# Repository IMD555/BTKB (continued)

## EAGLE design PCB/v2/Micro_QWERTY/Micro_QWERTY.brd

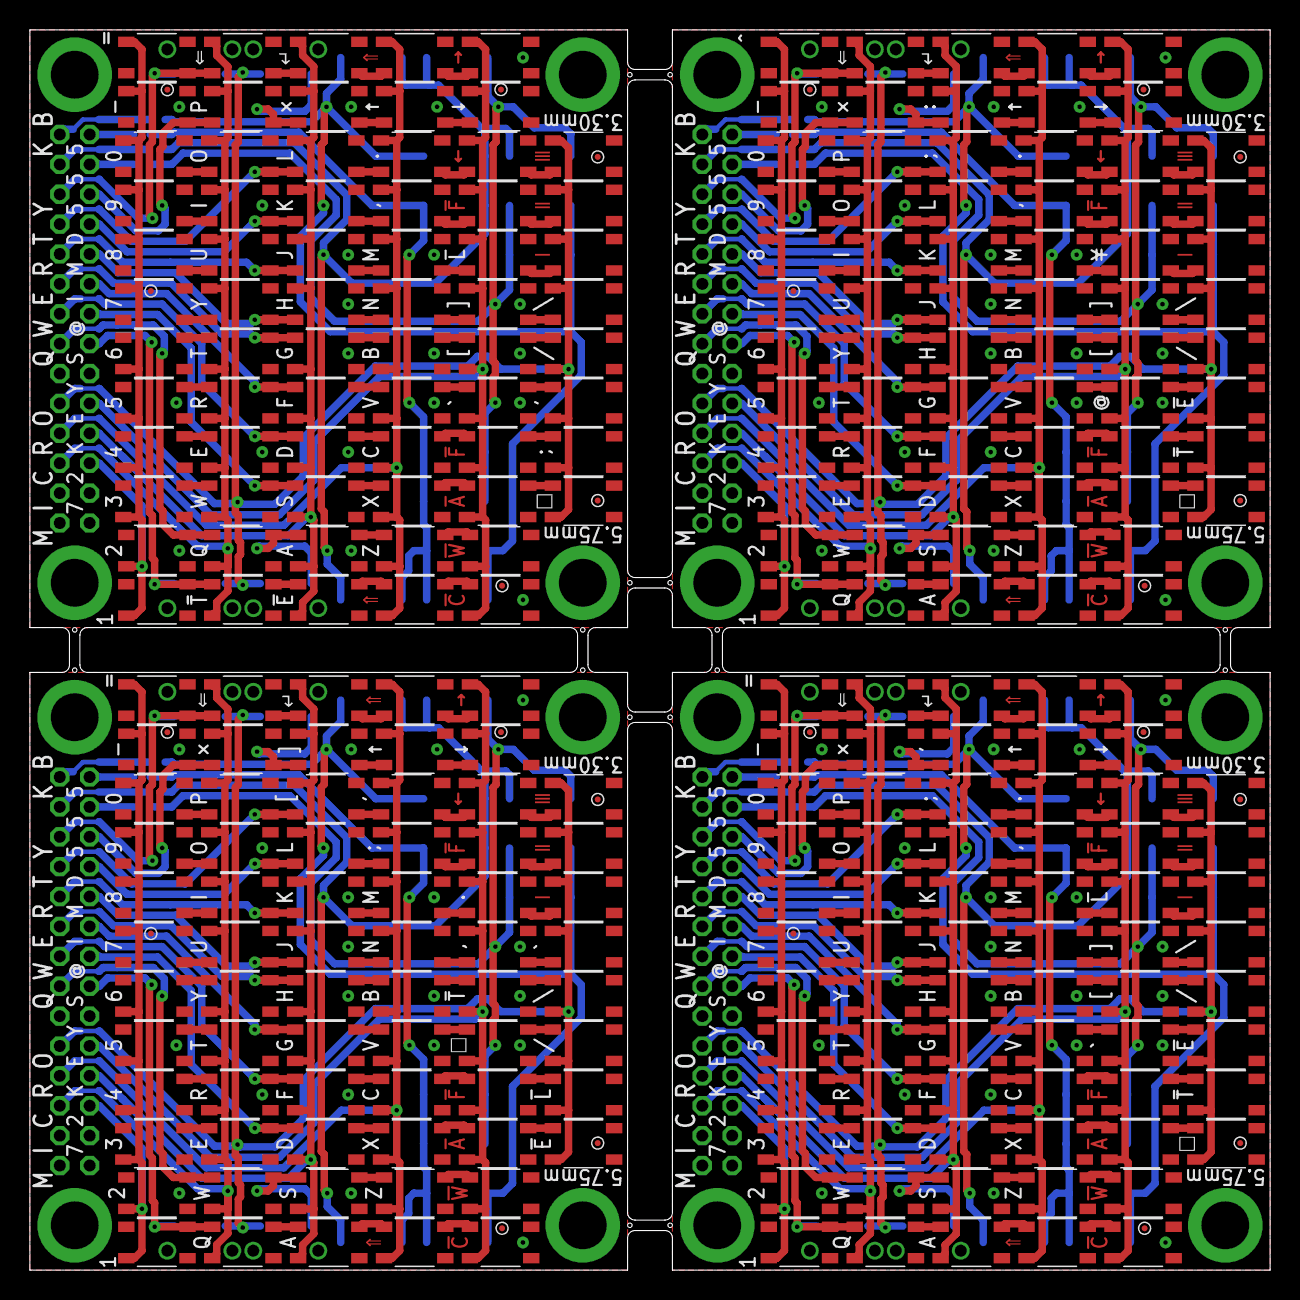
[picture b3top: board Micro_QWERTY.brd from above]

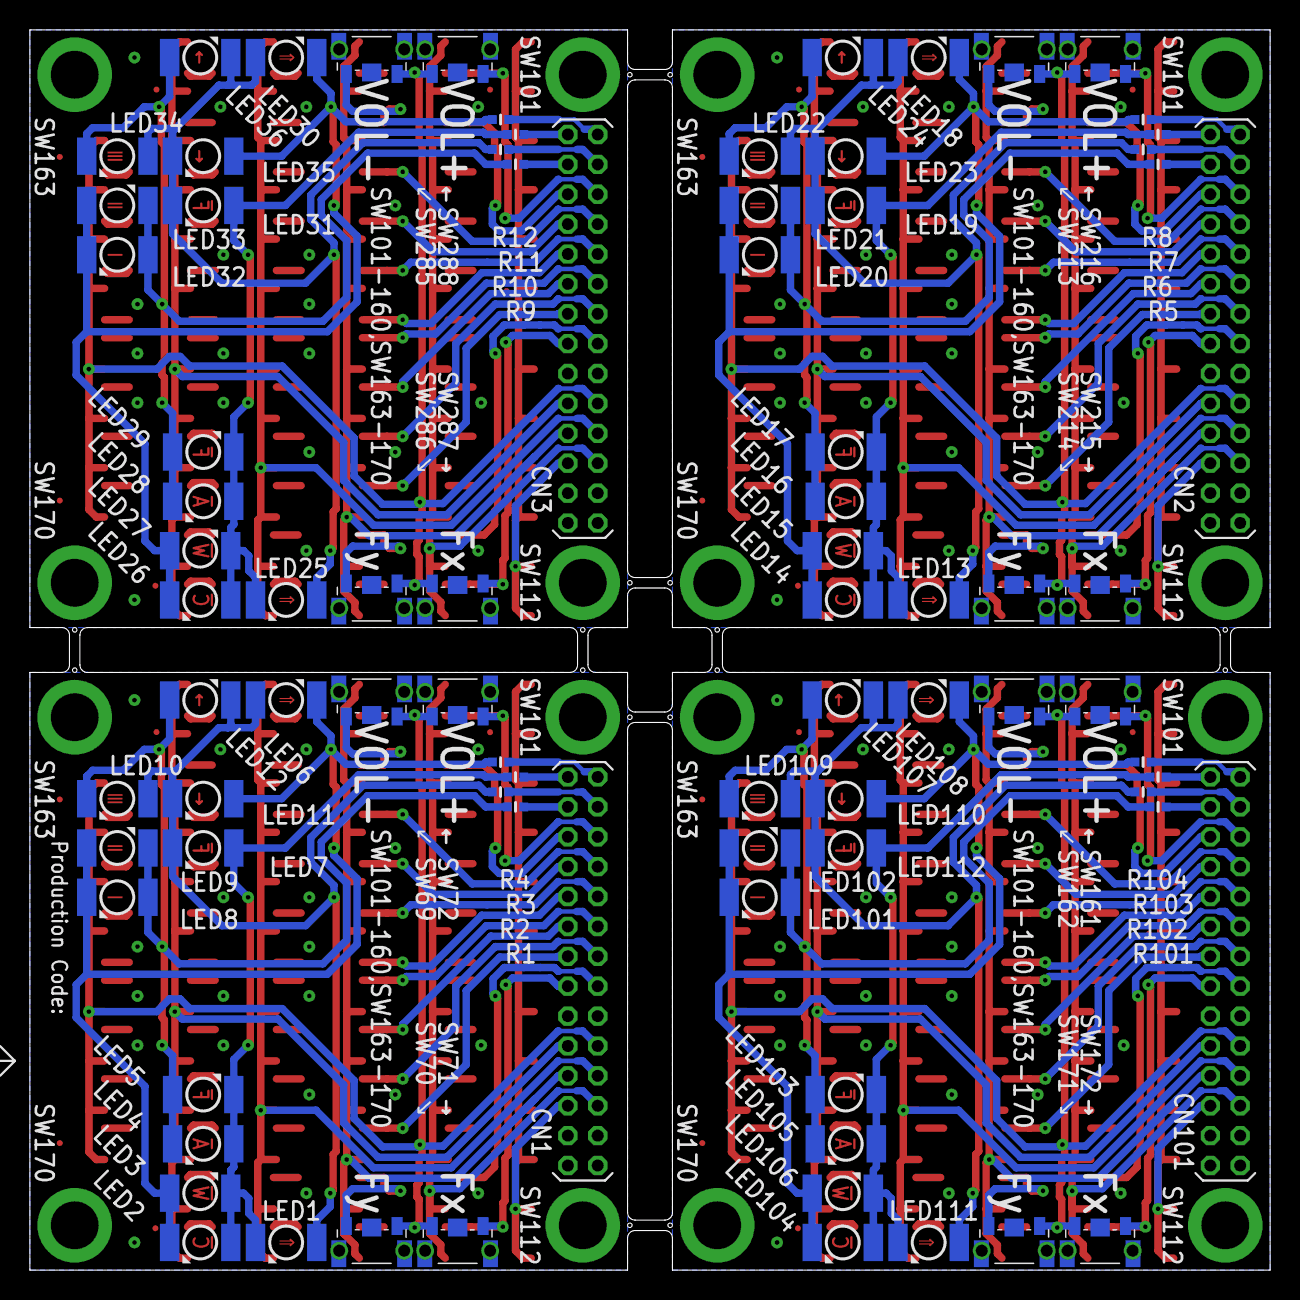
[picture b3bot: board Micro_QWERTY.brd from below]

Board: 2 copper layers, 83.0 x 83.0 mm, 380 parts (84 on the bottom side), 284 nets.

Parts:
CN1, CN2, CN3, CN101: 14X2R; 2MM_14X2_R
LED1, LED13, LED25, LED111: Shift_Left; P-LCC-2-TOPLED-RG-WINDOW
LED2, LED14, LED26, LED104: Ctrl; P-LCC-2-TOPLED-RG-WINDOW
LED3, LED15, LED27, LED106: Win; P-LCC-2-TOPLED-RG-WINDOW
LED4, LED16, LED28, LED105: Alt; P-LCC-2-TOPLED-RG-WINDOW
LED5, LED17, LED29, LED103: Fn_Left; P-LCC-2-TOPLED-RG-WINDOW
LED6, LED18, LED30, LED108: Shift_Right; P-LCC-2-TOPLED-RG-WINDOW
LED7, LED19, LED31, LED112: Fn_Right; P-LCC-2-TOPLED-RG-WINDOW
LED8, LED20, LED32, LED101: M1; P-LCC-2-TOPLED-RG-WINDOW
LED9, LED21, LED33, LED102: M2; P-LCC-2-TOPLED-RG-WINDOW
LED10, LED22, LED34, LED109: M3; P-LCC-2-TOPLED-RG-WINDOW
LED11, LED23, LED35, LED110: Cursor_Left; P-LCC-2-TOPLED-RG-WINDOW
LED12, LED24, LED36, LED107: Cursor_Right; P-LCC-2-TOPLED-RG-WINDOW
R1, R2, R3, R4, R5, R6, R7, R8, R9, R10, R11, R12, R101, R102, R103, R104: R0402-SS
SW1, SW73, SW112, SW217: SKRP(ALPS); TVAU10-025
SW2, SW3, SW4, SW5, SW6, SW7, SW8, SW9, SW10, SW11, SW12, SW13, SW14, SW15, SW16, SW17, SW18, SW19, SW20, SW21, SW22, SW23, SW24, SW25, SW26, SW27, SW28, SW29, SW30, SW31, SW32, SW33, SW34, SW35, SW36, SW37, SW38, SW39, SW40, SW41, SW42, SW43, SW44, SW45, SW46, SW47, SW48, SW49, SW50, SW51, SW52, SW53, SW54, SW55, SW56, SW57, SW58, SW59, SW60, SW61, SW62, SW63, SW64, SW65, SW66, SW67, SW68, SW74, SW75, SW76, SW77, SW78, SW79, SW80, SW81, SW82, SW83, SW84, SW85, SW86, SW87, SW88, SW89, SW90, SW91, SW92, SW93, SW94, SW95, SW96, SW97, SW98, SW99, SW100, SW101, SW102, SW103, SW104, SW105, SW106, SW107, SW108, SW109, SW110, SW111, SW113, SW114, SW115, SW116, SW117, SW118, SW119, SW120, SW121, SW122, SW123, SW124, SW125, SW126, SW127, SW128, SW129, SW130, SW131, SW132, SW133, SW134, SW135, SW136, SW137, SW138, SW139, SW140, SW141, SW142, SW143, SW144, SW145, SW146, SW147, SW148, SW149, SW150, SW151, SW152, SW153, SW154, SW155, SW156, SW157, SW158, SW159, SW160, SW163, SW164, SW165, SW166, SW167, SW168, SW169, SW170, SW173, SW174, SW175, SW176, SW177, SW178, SW179, SW180, SW181, SW182, SW183, SW184, SW185, SW186, SW187, SW188, SW189, SW190, SW191, SW192, SW193, SW194, SW195, SW196, SW197, SW198, SW199, SW200, SW201, SW202, SW203, SW204, SW205, SW206, SW207, SW208, SW209, SW210, SW211, SW212, SW218, SW219, SW220, SW221, SW222, SW223, SW224, SW225, SW226, SW227, SW228, SW229, SW230, SW231, SW232, SW233, SW234, SW235, SW236, SW237, SW238, SW239, SW240, SW241, SW242, SW243, SW244, SW245, SW246, SW247, SW248, SW249, SW250, SW251, SW252, SW253, SW254, SW255, SW256, SW257, SW258, SW259, SW260, SW261, SW262, SW263, SW264, SW265, SW266, SW267, SW268, SW269, SW270, SW271, SW272, SW273, SW274, SW275, SW276, SW277, SW278, SW279, SW280, SW281, SW282, SW283, SW284: SW_4PTVAU10-025; TVAU10-025
SW69, SW70, SW72, SW161, SW162, SW171, SW213, SW214, SW216, SW285, SW286, SW288: SW_WITH_EARTHX; THAM05
SW71, SW172, SW215, SW287: THAM05 or TS-018A; THAM05
U$1, U$2, U$3, U$4, U$5, U$6, U$7, U$8, U$9, U$10, U$11, U$12, U$13, U$14, U$15, U$16, U$17, U$18, U$19, U$20, U$21, U$22, U$23, U$24: PCB_CHECK

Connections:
C0: CN101.13, SW112.P$2, SW124.P$1, SW172.P$1
C1: CN101.14, SW111.P$2, SW123.P$1
C2: CN101.15, SW122.P$2, SW134.P$1
C3: CN101.16, SW121.P$2, SW133.P$1
C4: CN101.17, SW120.P$2, SW132.P$1
C5: CN101.18, SW119.P$2, SW131.P$1
C6: CN101.19, SW118.P$4, SW130.P$3
C7: CN101.20, SW117.P$4, SW129.P$3
C8: CN101.21, SW116.P$4, SW128.P$3
C9: CN101.22, SW115.P$4, SW127.P$3
C10: CN101.23, SW102.P$4, SW114.P$3
C11: CN101.24, SW101.P$4, SW113.P$3, SW161.P$2
C12: CN1.13, SW1.P$2, SW2.P$1, SW71.P$1
C13: CN1.14, SW6.P$2, SW7.P$1
C14: CN1.15, SW12.P$2, SW13.P$1
C15: CN1.16, SW18.P$2, SW19.P$1
C16: CN1.17, SW24.P$2, SW25.P$1
C17: CN1.18, SW30.P$2, SW31.P$1
C18: CN1.19, SW36.P$4, SW37.P$3
C19: CN1.20, SW42.P$4, SW43.P$3
C20: CN1.21, SW48.P$4, SW49.P$3
C21: CN1.22, SW54.P$4, SW55.P$3
C22: CN1.23, SW59.P$4, SW60.P$3
C23: CN1.24, SW64.P$4, SW65.P$3, SW72.P$2
C24: CN2.13, SW73.P$2, SW74.P$1, SW215.P$1
C25: CN2.14, SW78.P$2, SW79.P$1
C26: CN2.15, SW84.P$2, SW85.P$1
C27: CN2.16, SW90.P$2, SW91.P$1
C28: CN2.17, SW96.P$2, SW97.P$1
C29: CN2.18, SW174.P$2, SW175.P$1
C30: CN2.19, SW180.P$4, SW181.P$3
C31: CN2.20, SW186.P$4, SW187.P$3
C32: CN2.21, SW192.P$4, SW193.P$3
C33: CN2.22, SW198.P$4, SW199.P$3
C34: CN2.23, SW203.P$4, SW204.P$3
C35: CN2.24, SW208.P$4, SW209.P$3, SW216.P$2
C36: CN3.13, SW217.P$2, SW218.P$1, SW287.P$1
C37: CN3.14, SW222.P$2, SW223.P$1
C38: CN3.15, SW228.P$2, SW229.P$1
C39: CN3.16, SW234.P$2, SW235.P$1
C40: CN3.17, SW240.P$2, SW241.P$1
C41: CN3.18, SW246.P$2, SW247.P$1
C42: CN3.19, SW252.P$4, SW253.P$3
C43: CN3.20, SW258.P$4, SW259.P$3
C44: CN3.21, SW264.P$4, SW265.P$3
C45: CN3.22, SW270.P$4, SW271.P$3
C46: CN3.23, SW275.P$4, SW276.P$3
C47: CN3.24, SW280.P$4, SW281.P$3, SW288.P$2
GND: CN101.2, CN101.4, SW161.S1, SW161.S2, SW161.S3, SW161.S4, SW161.S5, SW162.S1, SW162.S2, SW162.S3, SW162.S4, SW162.S5, SW171.S1, SW171.S2, SW171.S3, SW171.S4, SW171.S5, SW172.S1, SW172.S2, SW172.S3, SW172.S4, SW172.S5
GND1: CN1.2, CN1.4, SW69.S1, SW69.S2, SW69.S3, SW69.S4, SW69.S5, SW70.S1, SW70.S2, SW70.S3, SW70.S4, SW70.S5, SW71.S1, SW71.S2, SW71.S3, SW71.S4, SW71.S5, SW72.S1, SW72.S2, SW72.S3, SW72.S4, SW72.S5
GND2: CN2.2, CN2.4, SW213.S1, SW213.S2, SW213.S3, SW213.S4, SW213.S5, SW214.S1, SW214.S2, SW214.S3, SW214.S4, SW214.S5, SW215.S1, SW215.S2, SW215.S3, SW215.S4, SW215.S5, SW216.S1, SW216.S2, SW216.S3, SW216.S4, SW216.S5
GND3: CN3.2, CN3.4, SW285.S1, SW285.S2, SW285.S3, SW285.S4, SW285.S5, SW286.S1, SW286.S2, SW286.S3, SW286.S4, SW286.S5, SW287.S1, SW287.S2, SW287.S3, SW287.S4, SW287.S5, SW288.S1, SW288.S2, SW288.S3, SW288.S4, SW288.S5
L0: CN101.28, R104.2
L1: CN101.27, R103.2
L2: CN101.26, R102.2
L3: CN101.25, R101.2
L4: CN1.26, R2.2
L5: CN1.28, R4.2
L6: CN1.25, R1.2
L7: CN1.27, R3.2
L8: CN2.26, R6.2
L9: CN2.28, R8.2
L10: CN2.25, R5.2
L11: CN2.27, R7.2
L12: CN3.26, R10.2
L13: CN3.28, R12.2
L14: CN3.25, R9.2
L15: CN3.27, R11.2
unnamed: LED107.C, LED108.A, LED109.A, LED110.C, LED111.A, LED112.C, R102.1
unnamed: LED101.A, LED102.C, LED103.A, LED105.C, LED107.A, LED109.C, R101.1
unnamed: LED103.C, LED104.A, LED105.A, LED106.C, LED111.C, LED112.A, R103.1
unnamed: LED101.C, LED102.A, LED104.C, LED106.A, LED108.C, LED110.A, R104.1
unnamed: SW123.P$2, SW135.P$1, SW171.P$2
unnamed: SW113.P$4, SW125.P$3
unnamed: SW114.P$4, SW126.P$3, SW162.P$1
unnamed: SW29.P$2, SW30.P$1
unnamed: SW106.P$4, SW118.P$3
unnamed: SW130.P$4, SW142.P$3
unnamed: SW154.P$4, SW166.P$3
unnamed: SW142.P$4, SW154.P$3
unnamed: SW105.P$4, SW117.P$3
unnamed: SW129.P$4, SW141.P$3
unnamed: SW153.P$4, SW165.P$3
unnamed: SW141.P$4, SW153.P$3
unnamed: SW104.P$4, SW116.P$3
unnamed: SW128.P$4, SW140.P$3
unnamed: SW152.P$4, SW164.P$3
unnamed: SW140.P$4, SW152.P$3
unnamed: SW103.P$4, SW115.P$3
unnamed: SW127.P$4, SW139.P$3
unnamed: SW151.P$4, SW163.P$3
unnamed: SW139.P$4, SW151.P$3
unnamed: SW31.P$2, SW32.P$1
unnamed: SW126.P$4, SW138.P$3
unnamed: SW32.P$2, SW33.P$1
unnamed: SW138.P$4, SW150.P$3
unnamed: SW33.P$2, SW34.P$1
unnamed: SW125.P$4, SW137.P$3
unnamed: SW2.P$2, SW3.P$1
unnamed: SW137.P$4, SW149.P$3
unnamed: SW3.P$2, SW4.P$1
unnamed: SW4.P$2, SW5.P$1
unnamed: SW8.P$2, SW9.P$1
unnamed: SW9.P$2, SW10.P$1
unnamed: SW11.P$2, SW12.P$1
unnamed: SW13.P$2, SW14.P$1
unnamed: SW14.P$2, SW15.P$1
unnamed: SW15.P$2, SW16.P$1
unnamed: SW107.P$2, SW119.P$1
unnamed: SW17.P$2, SW18.P$1
unnamed: SW131.P$2, SW143.P$1
unnamed: SW155.P$2, SW167.P$1
unnamed: SW143.P$2, SW155.P$1
unnamed: SW108.P$2, SW120.P$1
unnamed: SW19.P$2, SW20.P$1
unnamed: SW132.P$2, SW144.P$1
unnamed: SW156.P$2, SW168.P$1
unnamed: SW144.P$2, SW156.P$1
unnamed: SW109.P$2, SW121.P$1
unnamed: SW20.P$2, SW21.P$1
unnamed: SW133.P$2, SW145.P$1
unnamed: SW157.P$2, SW169.P$1
unnamed: SW145.P$2, SW157.P$1
unnamed: SW110.P$2, SW122.P$1
unnamed: SW21.P$2, SW22.P$1
unnamed: SW134.P$2, SW146.P$1
unnamed: SW158.P$2, SW170.P$1
unnamed: SW146.P$2, SW158.P$1
unnamed: SW23.P$2, SW24.P$1
unnamed: SW25.P$2, SW26.P$1
unnamed: SW26.P$2, SW27.P$1
unnamed: SW27.P$2, SW28.P$1
unnamed: LED1.A, LED6.A, LED7.C, LED10.A, LED11.C, LED12.C, R2.1
unnamed: LED4.C, LED5.A, LED8.A, LED9.C, LED10.C, LED12.A, R1.1
unnamed: LED1.C, LED2.A, LED3.C, LED4.A, LED5.C, LED7.A, R3.1
unnamed: SW135.P$2, SW147.P$1
unnamed: LED2.C, LED3.A, LED6.C, LED8.C, LED9.A, LED11.A, R4.1
unnamed: SW147.P$2, SW159.P$1
unnamed: SW41.P$4, SW42.P$3
unnamed: SW124.P$2, SW136.P$1
unnamed: SW136.P$2, SW148.P$1
unnamed: SW43.P$4, SW44.P$3
unnamed: SW148.P$2, SW160.P$1
unnamed: SW44.P$4, SW45.P$3
unnamed: SW45.P$4, SW46.P$3
unnamed: SW47.P$4, SW48.P$3
unnamed: SW49.P$4, SW50.P$3
unnamed: SW50.P$4, SW51.P$3
unnamed: SW51.P$4, SW52.P$3
unnamed: SW53.P$4, SW54.P$3
unnamed: SW55.P$4, SW56.P$3
unnamed: SW56.P$4, SW57.P$3
unnamed: SW57.P$4, SW58.P$3
unnamed: SW61.P$4, SW62.P$3
unnamed: SW62.P$4, SW63.P$3
unnamed: SW66.P$4, SW67.P$3
unnamed: SW67.P$4, SW68.P$3
unnamed: SW35.P$4, SW36.P$3
unnamed: SW37.P$4, SW38.P$3
unnamed: SW38.P$4, SW39.P$3
unnamed: SW39.P$4, SW40.P$3
unnamed: SW7.P$2, SW8.P$1, SW70.P$2
unnamed: SW65.P$4, SW66.P$3
unnamed: SW60.P$4, SW61.P$3, SW69.P$1
unnamed: SW173.P$2, SW174.P$1
unnamed: SW175.P$2, SW176.P$1
unnamed: SW176.P$2, SW177.P$1
unnamed: SW177.P$2, SW178.P$1
unnamed: SW74.P$2, SW75.P$1
unnamed: SW75.P$2, SW76.P$1
unnamed: SW76.P$2, SW77.P$1
unnamed: SW80.P$2, SW81.P$1
unnamed: SW81.P$2, SW82.P$1
unnamed: SW83.P$2, SW84.P$1
unnamed: SW85.P$2, SW86.P$1
unnamed: SW86.P$2, SW87.P$1
unnamed: SW87.P$2, SW88.P$1
unnamed: SW89.P$2, SW90.P$1
unnamed: SW91.P$2, SW92.P$1
unnamed: SW92.P$2, SW93.P$1
unnamed: SW93.P$2, SW94.P$1
unnamed: SW95.P$2, SW96.P$1
unnamed: SW97.P$2, SW98.P$1
unnamed: SW98.P$2, SW99.P$1
unnamed: SW99.P$2, SW100.P$1
unnamed: LED13.A, LED18.A, LED19.C, LED22.A, LED23.C, LED24.C, R6.1
unnamed: LED16.C, LED17.A, LED20.A, LED21.C, LED22.C, LED24.A, R5.1
unnamed: LED13.C, LED14.A, LED15.C, LED16.A, LED17.C, LED19.A, R7.1
unnamed: LED14.C, LED15.A, LED18.C, LED20.C, LED21.A, LED23.A, R8.1
unnamed: SW185.P$4, SW186.P$3
unnamed: SW187.P$4, SW188.P$3
unnamed: SW188.P$4, SW189.P$3
unnamed: SW189.P$4, SW190.P$3
unnamed: SW191.P$4, SW192.P$3
unnamed: SW193.P$4, SW194.P$3
unnamed: SW194.P$4, SW195.P$3
unnamed: SW195.P$4, SW196.P$3
unnamed: SW197.P$4, SW198.P$3
unnamed: SW199.P$4, SW200.P$3
unnamed: SW200.P$4, SW201.P$3
unnamed: SW201.P$4, SW202.P$3
unnamed: SW205.P$4, SW206.P$3
unnamed: SW206.P$4, SW207.P$3
unnamed: SW210.P$4, SW211.P$3
unnamed: SW211.P$4, SW212.P$3
unnamed: SW179.P$4, SW180.P$3
unnamed: SW181.P$4, SW182.P$3
unnamed: SW182.P$4, SW183.P$3
unnamed: SW183.P$4, SW184.P$3
unnamed: SW79.P$2, SW80.P$1, SW214.P$2
unnamed: SW209.P$4, SW210.P$3
unnamed: SW204.P$4, SW205.P$3, SW213.P$1
unnamed: SW245.P$2, SW246.P$1
unnamed: SW247.P$2, SW248.P$1
unnamed: SW248.P$2, SW249.P$1
unnamed: SW249.P$2, SW250.P$1
unnamed: SW218.P$2, SW219.P$1
unnamed: SW219.P$2, SW220.P$1
unnamed: SW220.P$2, SW221.P$1
unnamed: SW224.P$2, SW225.P$1
unnamed: SW225.P$2, SW226.P$1
unnamed: SW227.P$2, SW228.P$1
unnamed: SW229.P$2, SW230.P$1
unnamed: SW230.P$2, SW231.P$1
unnamed: SW231.P$2, SW232.P$1
unnamed: SW233.P$2, SW234.P$1
unnamed: SW235.P$2, SW236.P$1
unnamed: SW236.P$2, SW237.P$1
unnamed: SW237.P$2, SW238.P$1
unnamed: SW239.P$2, SW240.P$1
unnamed: SW241.P$2, SW242.P$1
unnamed: SW242.P$2, SW243.P$1
unnamed: SW243.P$2, SW244.P$1
unnamed: LED25.A, LED30.A, LED31.C, LED34.A, LED35.C, LED36.C, R10.1
unnamed: LED28.C, LED29.A, LED32.A, LED33.C, LED34.C, LED36.A, R9.1
unnamed: LED25.C, LED26.A, LED27.C, LED28.A, LED29.C, LED31.A, R11.1
unnamed: LED26.C, LED27.A, LED30.C, LED32.C, LED33.A, LED35.A, R12.1
unnamed: SW257.P$4, SW258.P$3
unnamed: SW259.P$4, SW260.P$3
unnamed: SW260.P$4, SW261.P$3
unnamed: SW261.P$4, SW262.P$3
unnamed: SW263.P$4, SW264.P$3
unnamed: SW265.P$4, SW266.P$3
unnamed: SW266.P$4, SW267.P$3
unnamed: SW267.P$4, SW268.P$3
unnamed: SW269.P$4, SW270.P$3
unnamed: SW271.P$4, SW272.P$3
unnamed: SW272.P$4, SW273.P$3
unnamed: SW273.P$4, SW274.P$3
unnamed: SW277.P$4, SW278.P$3
unnamed: SW278.P$4, SW279.P$3
unnamed: SW282.P$4, SW283.P$3
unnamed: SW283.P$4, SW284.P$3
unnamed: SW251.P$4, SW252.P$3
unnamed: SW253.P$4, SW254.P$3
unnamed: SW254.P$4, SW255.P$3
unnamed: SW255.P$4, SW256.P$3
unnamed: SW223.P$2, SW224.P$1, SW286.P$2
unnamed: SW281.P$4, SW282.P$3
unnamed: SW276.P$4, SW277.P$3, SW285.P$1
R0: CN101.5, SW101.P$1, SW102.P$1, SW103.P$1, SW104.P$1, SW105.P$1, SW106.P$1, SW107.P$3, SW108.P$3, SW109.P$3, SW110.P$3, SW111.P$3, SW112.P$3
R1: CN101.6, SW113.P$1, SW114.P$1, SW115.P$1, SW116.P$1, SW117.P$1, SW118.P$1, SW119.P$3, SW120.P$3, SW121.P$3, SW122.P$3, SW123.P$3, SW124.P$3
R2: CN101.7, SW125.P$1, SW126.P$1, SW127.P$1, SW128.P$1, SW129.P$1, SW130.P$1, SW131.P$3, SW132.P$3, SW133.P$3, SW134.P$3, SW135.P$3, SW136.P$3
R3: CN101.8, SW137.P$1, SW138.P$1, SW139.P$1, SW140.P$1, SW141.P$1, SW142.P$1, SW143.P$3, SW144.P$3, SW145.P$3, SW146.P$3, SW147.P$3, SW148.P$3
R4: CN101.9, SW149.P$1, SW150.P$1, SW151.P$1, SW152.P$1, SW153.P$1, SW154.P$1, SW155.P$3, SW156.P$3, SW157.P$3, SW158.P$3, SW159.P$3, SW160.P$3
R5: CN101.10, SW161.P$1, SW162.P$2, SW163.P$1, SW164.P$1, SW165.P$1, SW166.P$1, SW167.P$3, SW168.P$3, SW169.P$3, SW170.P$3, SW171.P$1, SW172.P$2
R6: CN1.5, SW1.P$3, SW6.P$3, SW11.P$3, SW17.P$3, SW23.P$3, SW29.P$3, SW35.P$1, SW41.P$1, SW47.P$1, SW53.P$1, SW59.P$1, SW64.P$1
R7: CN1.6, SW2.P$3, SW7.P$3, SW12.P$3, SW18.P$3, SW24.P$3, SW30.P$3, SW36.P$1, SW42.P$1, SW48.P$1, SW54.P$1, SW60.P$1, SW65.P$1
R8: CN1.7, SW3.P$3, SW8.P$3, SW13.P$3, SW19.P$3, SW25.P$3, SW31.P$3, SW37.P$1, SW43.P$1, SW49.P$1, SW55.P$1, SW61.P$1, SW66.P$1
R9: CN1.8, SW4.P$3, SW9.P$3, SW14.P$3, SW20.P$3, SW26.P$3, SW32.P$3, SW38.P$1, SW44.P$1, SW50.P$1, SW56.P$1, SW62.P$1, SW67.P$1
R10: CN1.9, SW5.P$3, SW10.P$3, SW15.P$3, SW21.P$3, SW27.P$3, SW33.P$3, SW39.P$1, SW45.P$1, SW51.P$1, SW57.P$1, SW63.P$1, SW68.P$1
R11: CN1.10, SW16.P$3, SW22.P$3, SW28.P$3, SW34.P$3, SW40.P$1, SW46.P$1, SW52.P$1, SW58.P$1, SW69.P$2, SW70.P$1, SW71.P$2, SW72.P$1
R12: CN2.5, SW73.P$3, SW78.P$3, SW83.P$3, SW89.P$3, SW95.P$3, SW173.P$3, SW179.P$1, SW185.P$1, SW191.P$1, SW197.P$1, SW203.P$1, SW208.P$1
R13: CN2.6, SW74.P$3, SW79.P$3, SW84.P$3, SW90.P$3, SW96.P$3, SW174.P$3, SW180.P$1, SW186.P$1, SW192.P$1, SW198.P$1, SW204.P$1, SW209.P$1
R14: CN2.7, SW75.P$3, SW80.P$3, SW85.P$3, SW91.P$3, SW97.P$3, SW175.P$3, SW181.P$1, SW187.P$1, SW193.P$1, SW199.P$1, SW205.P$1, SW210.P$1
R15: CN2.8, SW76.P$3, SW81.P$3, SW86.P$3, SW92.P$3, SW98.P$3, SW176.P$3, SW182.P$1, SW188.P$1, SW194.P$1, SW200.P$1, SW206.P$1, SW211.P$1
R16: CN2.9, SW77.P$3, SW82.P$3, SW87.P$3, SW93.P$3, SW99.P$3, SW177.P$3, SW183.P$1, SW189.P$1, SW195.P$1, SW201.P$1, SW207.P$1, SW212.P$1
R17: CN2.10, SW88.P$3, SW94.P$3, SW100.P$3, SW178.P$3, SW184.P$1, SW190.P$1, SW196.P$1, SW202.P$1, SW213.P$2, SW214.P$1, SW215.P$2, SW216.P$1
R18: CN3.5, SW217.P$3, SW222.P$3, SW227.P$3, SW233.P$3, SW239.P$3, SW245.P$3, SW251.P$1, SW257.P$1, SW263.P$1, SW269.P$1, SW275.P$1, SW280.P$1
R19: CN3.6, SW218.P$3, SW223.P$3, SW228.P$3, SW234.P$3, SW240.P$3, SW246.P$3, SW252.P$1, SW258.P$1, SW264.P$1, SW270.P$1, SW276.P$1, SW281.P$1
R20: CN3.7, SW219.P$3, SW224.P$3, SW229.P$3, SW235.P$3, SW241.P$3, SW247.P$3, SW253.P$1, SW259.P$1, SW265.P$1, SW271.P$1, SW277.P$1, SW282.P$1
R21: CN3.8, SW220.P$3, SW225.P$3, SW230.P$3, SW236.P$3, SW242.P$3, SW248.P$3, SW254.P$1, SW260.P$1, SW266.P$1, SW272.P$1, SW278.P$1, SW283.P$1
R22: CN3.9, SW221.P$3, SW226.P$3, SW231.P$3, SW237.P$3, SW243.P$3, SW249.P$3, SW255.P$1, SW261.P$1, SW267.P$1, SW273.P$1, SW279.P$1, SW284.P$1
R23: CN3.10, SW232.P$3, SW238.P$3, SW244.P$3, SW250.P$3, SW256.P$1, SW262.P$1, SW268.P$1, SW274.P$1, SW285.P$2, SW286.P$1, SW287.P$2, SW288.P$1

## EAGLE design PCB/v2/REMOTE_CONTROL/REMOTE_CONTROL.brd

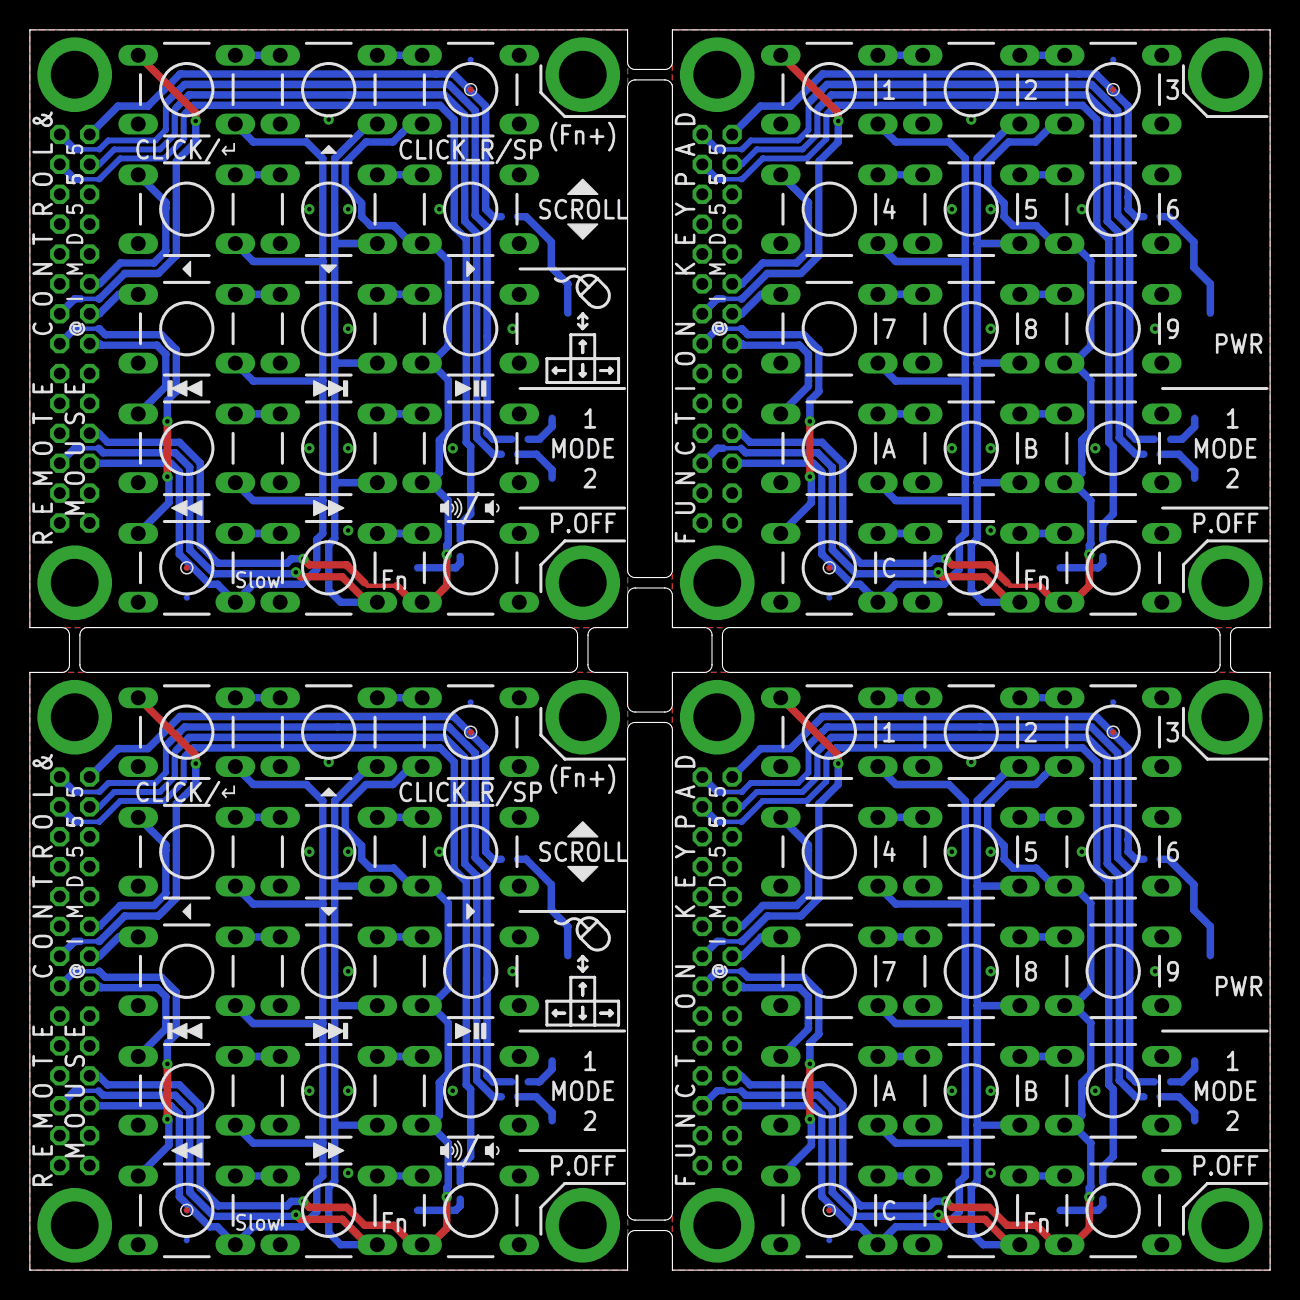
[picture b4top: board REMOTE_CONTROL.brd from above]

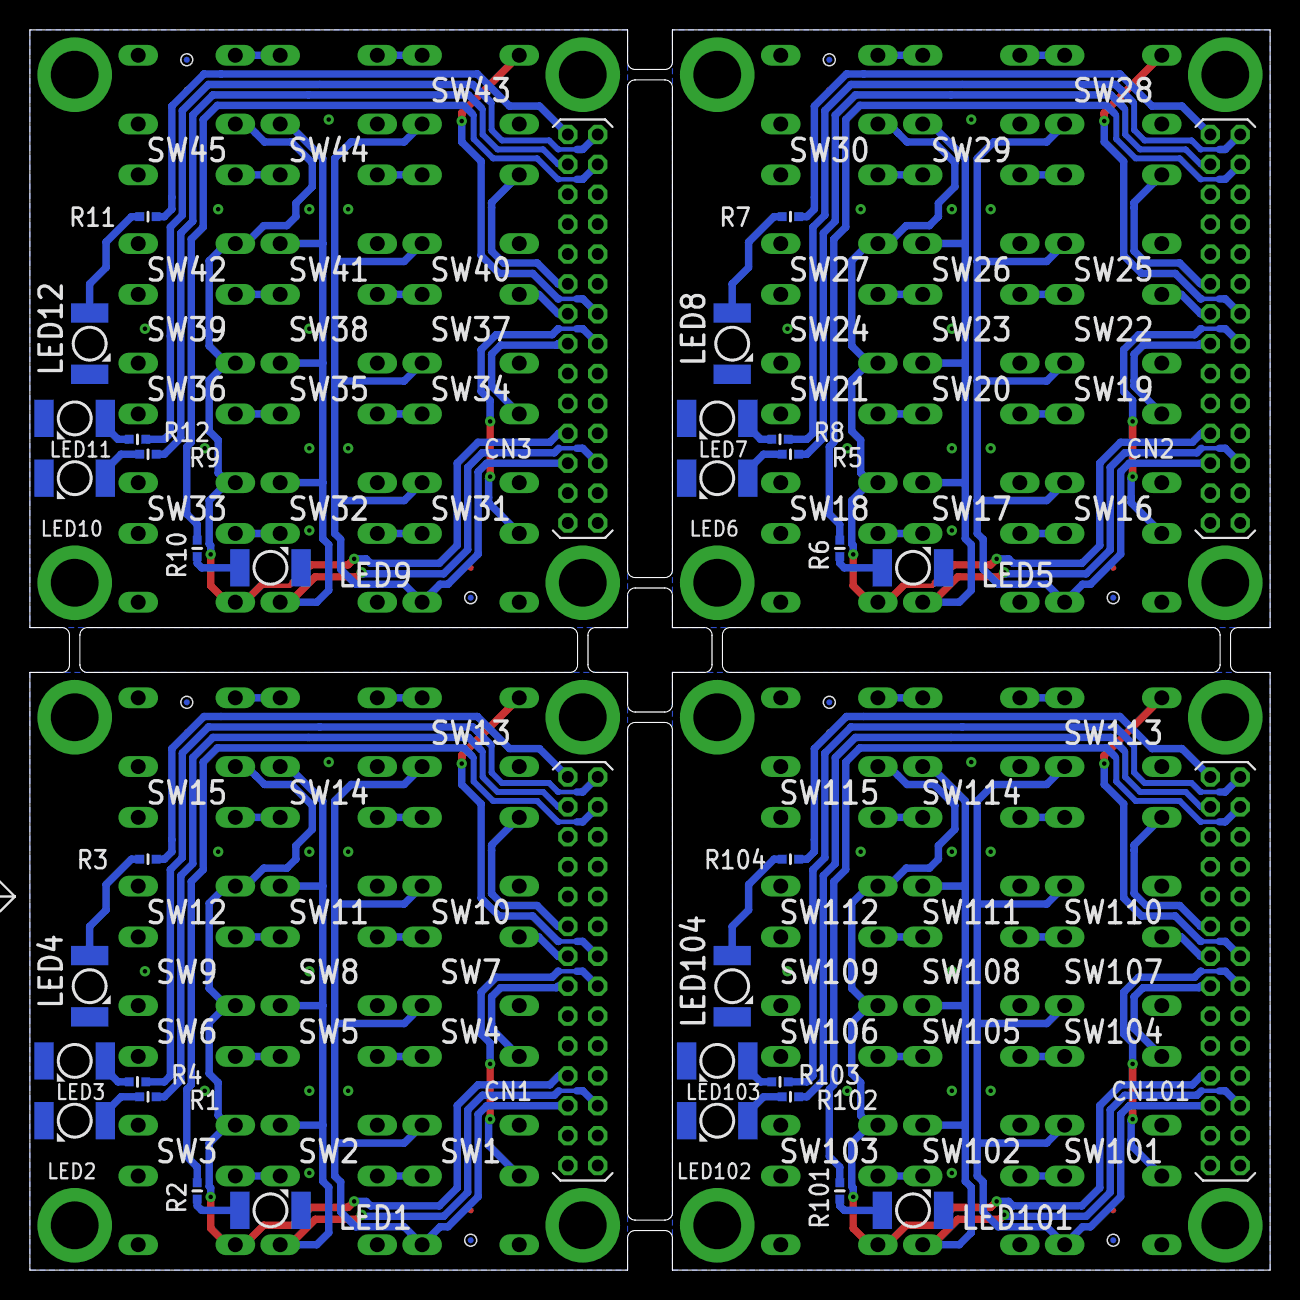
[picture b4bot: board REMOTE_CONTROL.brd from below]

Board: 2 copper layers, 83.0 x 83.0 mm, 112 parts (44 on the bottom side), 108 nets.

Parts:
CN1, CN2, CN3, CN101: 14X2R; 2MM_14X2_R
LED1, LED2, LED3, LED4, LED5, LED6, LED7, LED8, LED9, LED10, LED11, LED12, LED101, LED102, LED103, LED104: P-LCC-2-TOPLED-RG
R1, R2, R3, R4, R5, R6, R7, R8, R9, R10, R11, R12, R101, R102, R103, R104: R0402-SS
SW1, SW2, SW3, SW4, SW5, SW6, SW7, SW8, SW9, SW10, SW11, SW12, SW13, SW14, SW15, SW16, SW17, SW18, SW19, SW20, SW21, SW22, SW23, SW24, SW25, SW26, SW27, SW28, SW29, SW30, SW31, SW32, SW33, SW34, SW35, SW36, SW37, SW38, SW39, SW40, SW41, SW42, SW43, SW44, SW45, SW101, SW102, SW103, SW104, SW105, SW106, SW107, SW108, SW109, SW110, SW111, SW112, SW113, SW114, SW115: DTS-6
U$1, U$2, U$3, U$4, U$5, U$6, U$7, U$8, U$9, U$10, U$11, U$12, U$13, U$14, U$15, U$16: PCB_CHECK

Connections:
C0: CN101.13, SW104.1
C1: CN101.14, SW101.1
C2: CN101.15, SW107.1
C3: CN101.16, SW113.1
C4: CN101.17, SW110.1
C12: CN1.13, SW4.1
C13: CN1.14, SW1.1
C14: CN1.15, SW7.1
C15: CN1.16, SW13.1
C16: CN1.17, SW10.1
C24: CN2.13, SW19.1
C25: CN2.14, SW16.1
C26: CN2.15, SW22.1
C27: CN2.16, SW28.1
C28: CN2.17, SW25.1
C36: CN3.13, SW34.1
C37: CN3.14, SW31.1
C38: CN3.15, SW37.1
C39: CN3.16, SW43.1
C40: CN3.17, SW40.1
GND: CN101.2, CN101.4, LED101.C, LED102.C, LED103.C, LED104.C
GND1: CN1.2, CN1.4, LED1.C, LED2.C, LED3.C, LED4.C
GND2: CN2.2, CN2.4, LED5.C, LED6.C, LED7.C, LED8.C
GND3: CN3.2, CN3.4, LED9.C, LED10.C, LED11.C, LED12.C
L0: CN101.25, R102.2
L1: CN101.26, R101.2
L2: CN101.27, R104.2
L3: CN101.28, R103.2
L4: CN1.26, R2.2
L5: CN1.28, R4.2
L6: CN1.25, R1.2
L7: CN1.27, R3.2
L8: CN2.26, R6.2
L9: CN2.28, R8.2
L10: CN2.25, R5.2
L11: CN2.27, R7.2
L12: CN3.26, R10.2
L13: CN3.28, R12.2
L14: CN3.25, R9.2
L15: CN3.27, R11.2
unnamed: LED104.A, R104.1
unnamed: SW114.2, SW115.1
unnamed: LED103.A, R103.1
unnamed: SW111.2, SW112.1
unnamed: SW108.2, SW109.1
unnamed: LED102.A, R102.1
unnamed: LED101.A, R101.1
unnamed: SW102.2, SW103.1
unnamed: SW105.2, SW106.1
unnamed: SW14.2, SW15.1
unnamed: SW110.2, SW111.1
unnamed: SW107.2, SW108.1
unnamed: SW104.2, SW105.1
unnamed: SW101.2, SW102.1
unnamed: SW113.2, SW114.1
unnamed: SW11.2, SW12.1
unnamed: SW8.2, SW9.1
unnamed: SW2.2, SW3.1
unnamed: SW5.2, SW6.1
unnamed: SW10.2, SW11.1
unnamed: SW7.2, SW8.1
unnamed: SW4.2, SW5.1
unnamed: SW1.2, SW2.1
unnamed: SW13.2, SW14.1
unnamed: LED4.A, R3.1
unnamed: LED3.A, R4.1
unnamed: LED2.A, R1.1
unnamed: LED1.A, R2.1
unnamed: SW29.2, SW30.1
unnamed: SW26.2, SW27.1
unnamed: SW23.2, SW24.1
unnamed: SW17.2, SW18.1
unnamed: SW20.2, SW21.1
unnamed: SW25.2, SW26.1
unnamed: SW22.2, SW23.1
unnamed: SW19.2, SW20.1
unnamed: SW16.2, SW17.1
unnamed: SW28.2, SW29.1
unnamed: LED8.A, R7.1
unnamed: LED7.A, R8.1
unnamed: LED6.A, R5.1
unnamed: LED5.A, R6.1
unnamed: SW44.2, SW45.1
unnamed: SW41.2, SW42.1
unnamed: SW38.2, SW39.1
unnamed: SW32.2, SW33.1
unnamed: SW35.2, SW36.1
unnamed: SW40.2, SW41.1
unnamed: SW37.2, SW38.1
unnamed: SW34.2, SW35.1
unnamed: SW31.2, SW32.1
unnamed: SW43.2, SW44.1
unnamed: LED12.A, R11.1
unnamed: LED11.A, R12.1
unnamed: LED10.A, R9.1
unnamed: LED9.A, R10.1
R0: CN101.5, SW101.4, SW104.4, SW107.4, SW110.4, SW113.4
R1: CN101.6, SW102.4, SW105.4, SW108.4, SW111.4, SW114.4
R2: CN101.7, SW103.3, SW106.3, SW109.3, SW112.3, SW115.3
R6: CN1.5, SW1.4, SW4.4, SW7.4, SW10.4, SW13.4
R7: CN1.6, SW2.4, SW5.4, SW8.4, SW11.4, SW14.4
R8: CN1.7, SW3.3, SW6.3, SW9.3, SW12.3, SW15.3
R12: CN2.5, SW16.4, SW19.4, SW22.4, SW25.4, SW28.4
R13: CN2.6, SW17.4, SW20.4, SW23.4, SW26.4, SW29.4
R14: CN2.7, SW18.3, SW21.3, SW24.3, SW27.3, SW30.3
R18: CN3.5, SW31.4, SW34.4, SW37.4, SW40.4, SW43.4
R19: CN3.6, SW32.4, SW35.4, SW38.4, SW41.4, SW44.4
R20: CN3.7, SW33.3, SW36.3, SW39.3, SW42.3, SW45.3
